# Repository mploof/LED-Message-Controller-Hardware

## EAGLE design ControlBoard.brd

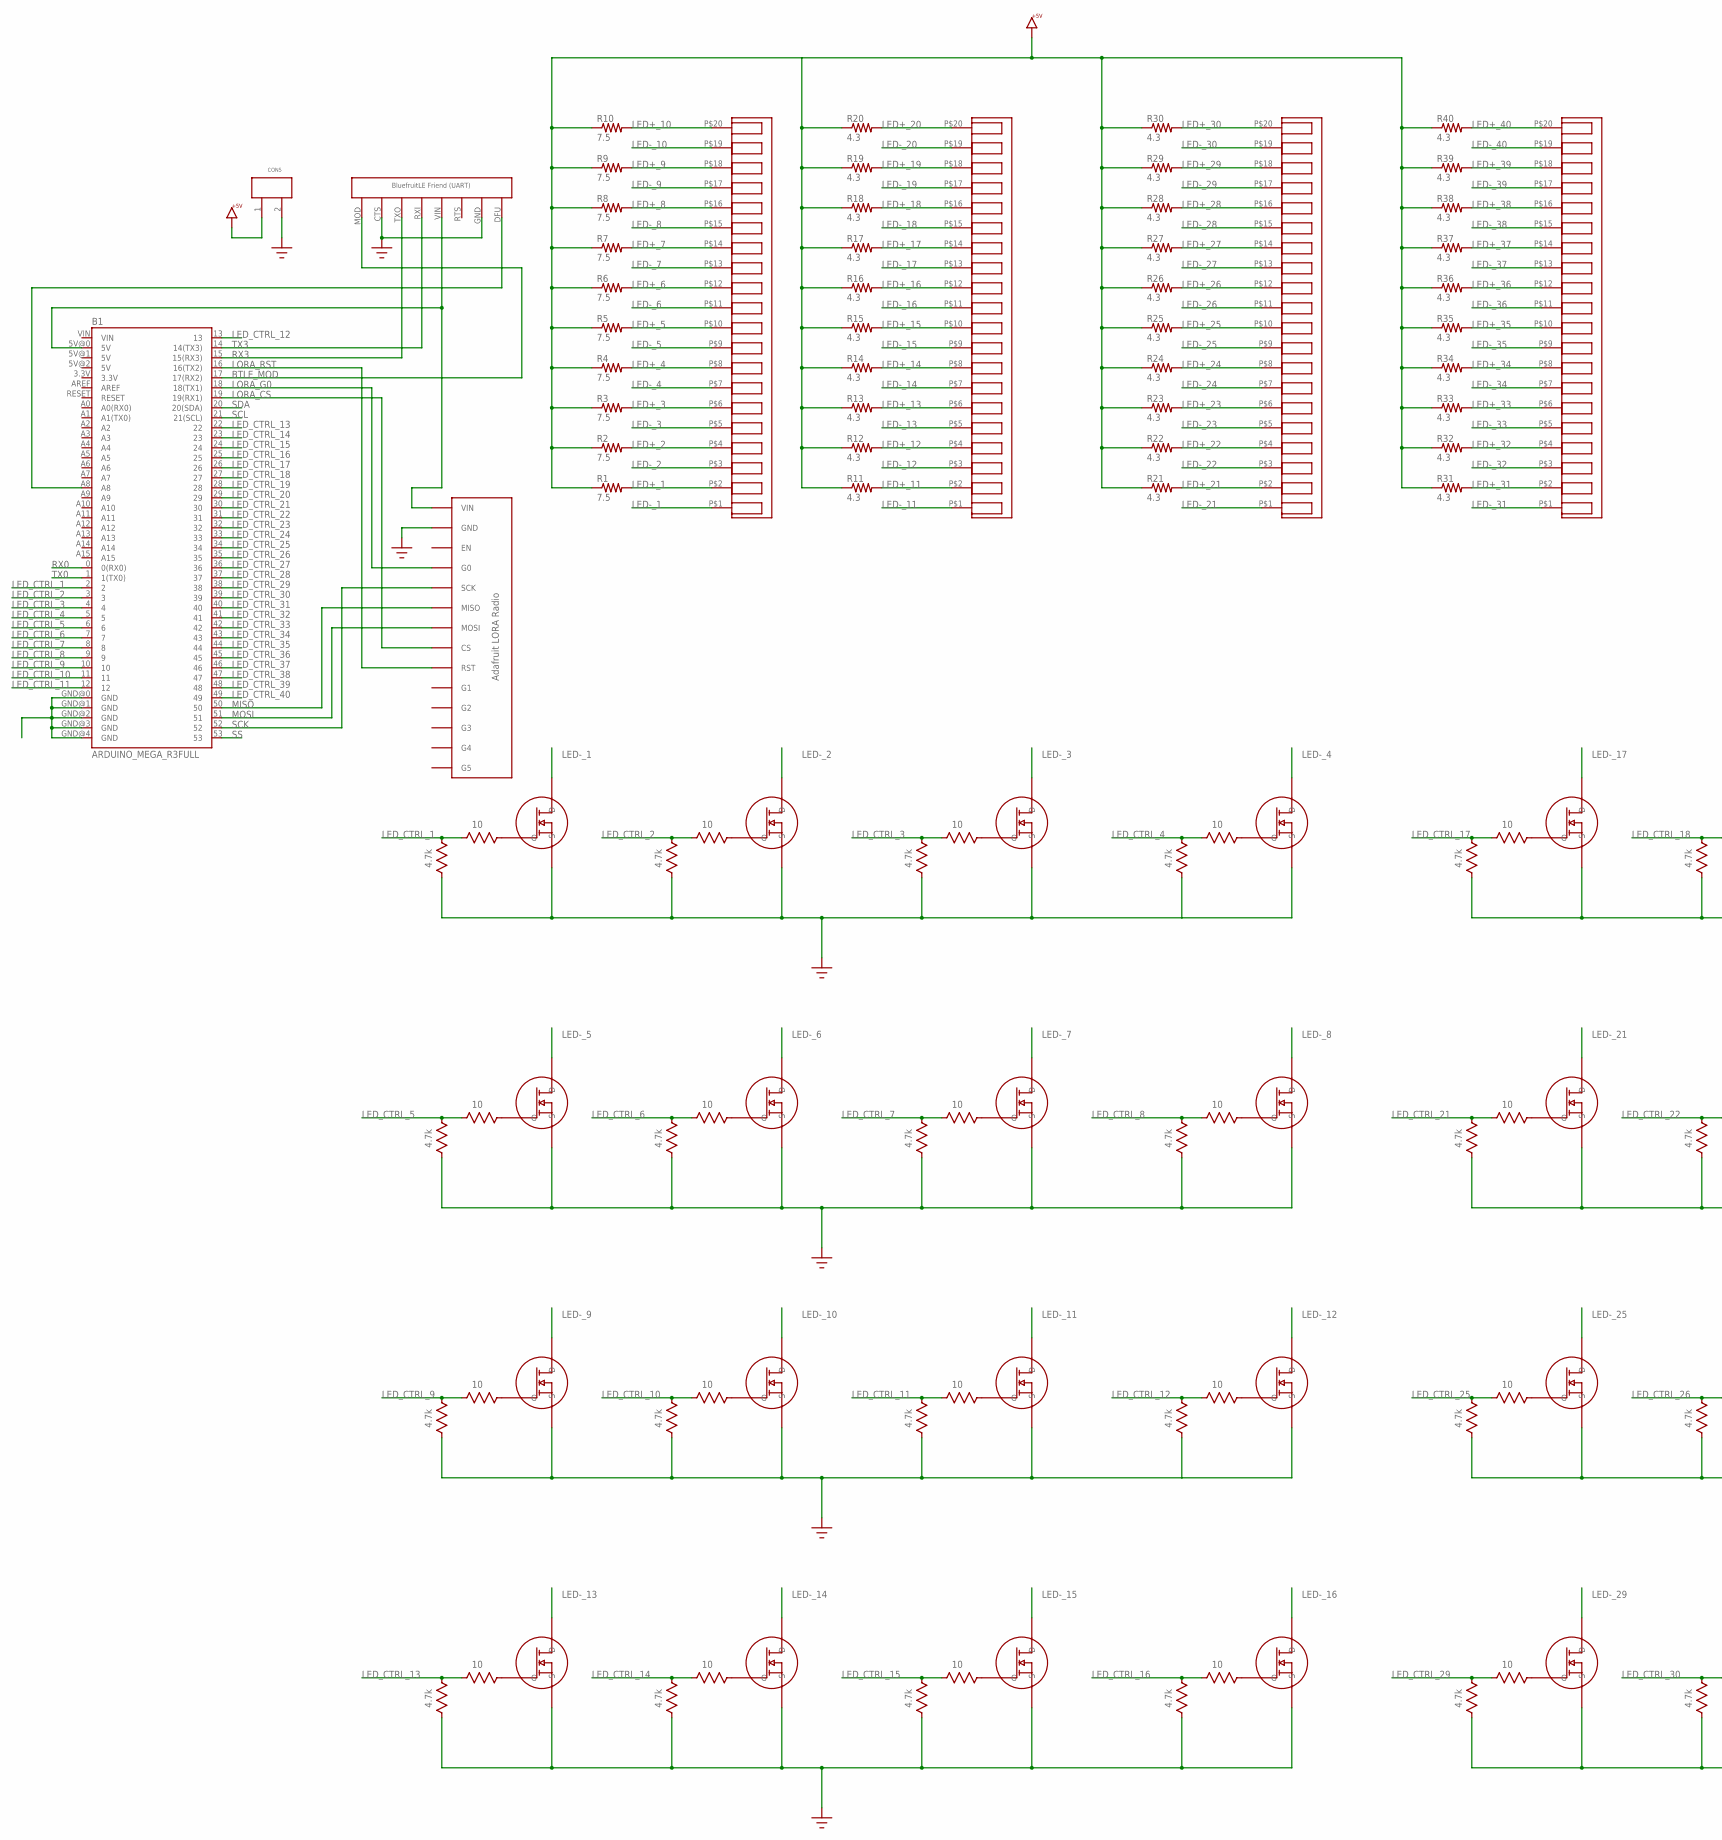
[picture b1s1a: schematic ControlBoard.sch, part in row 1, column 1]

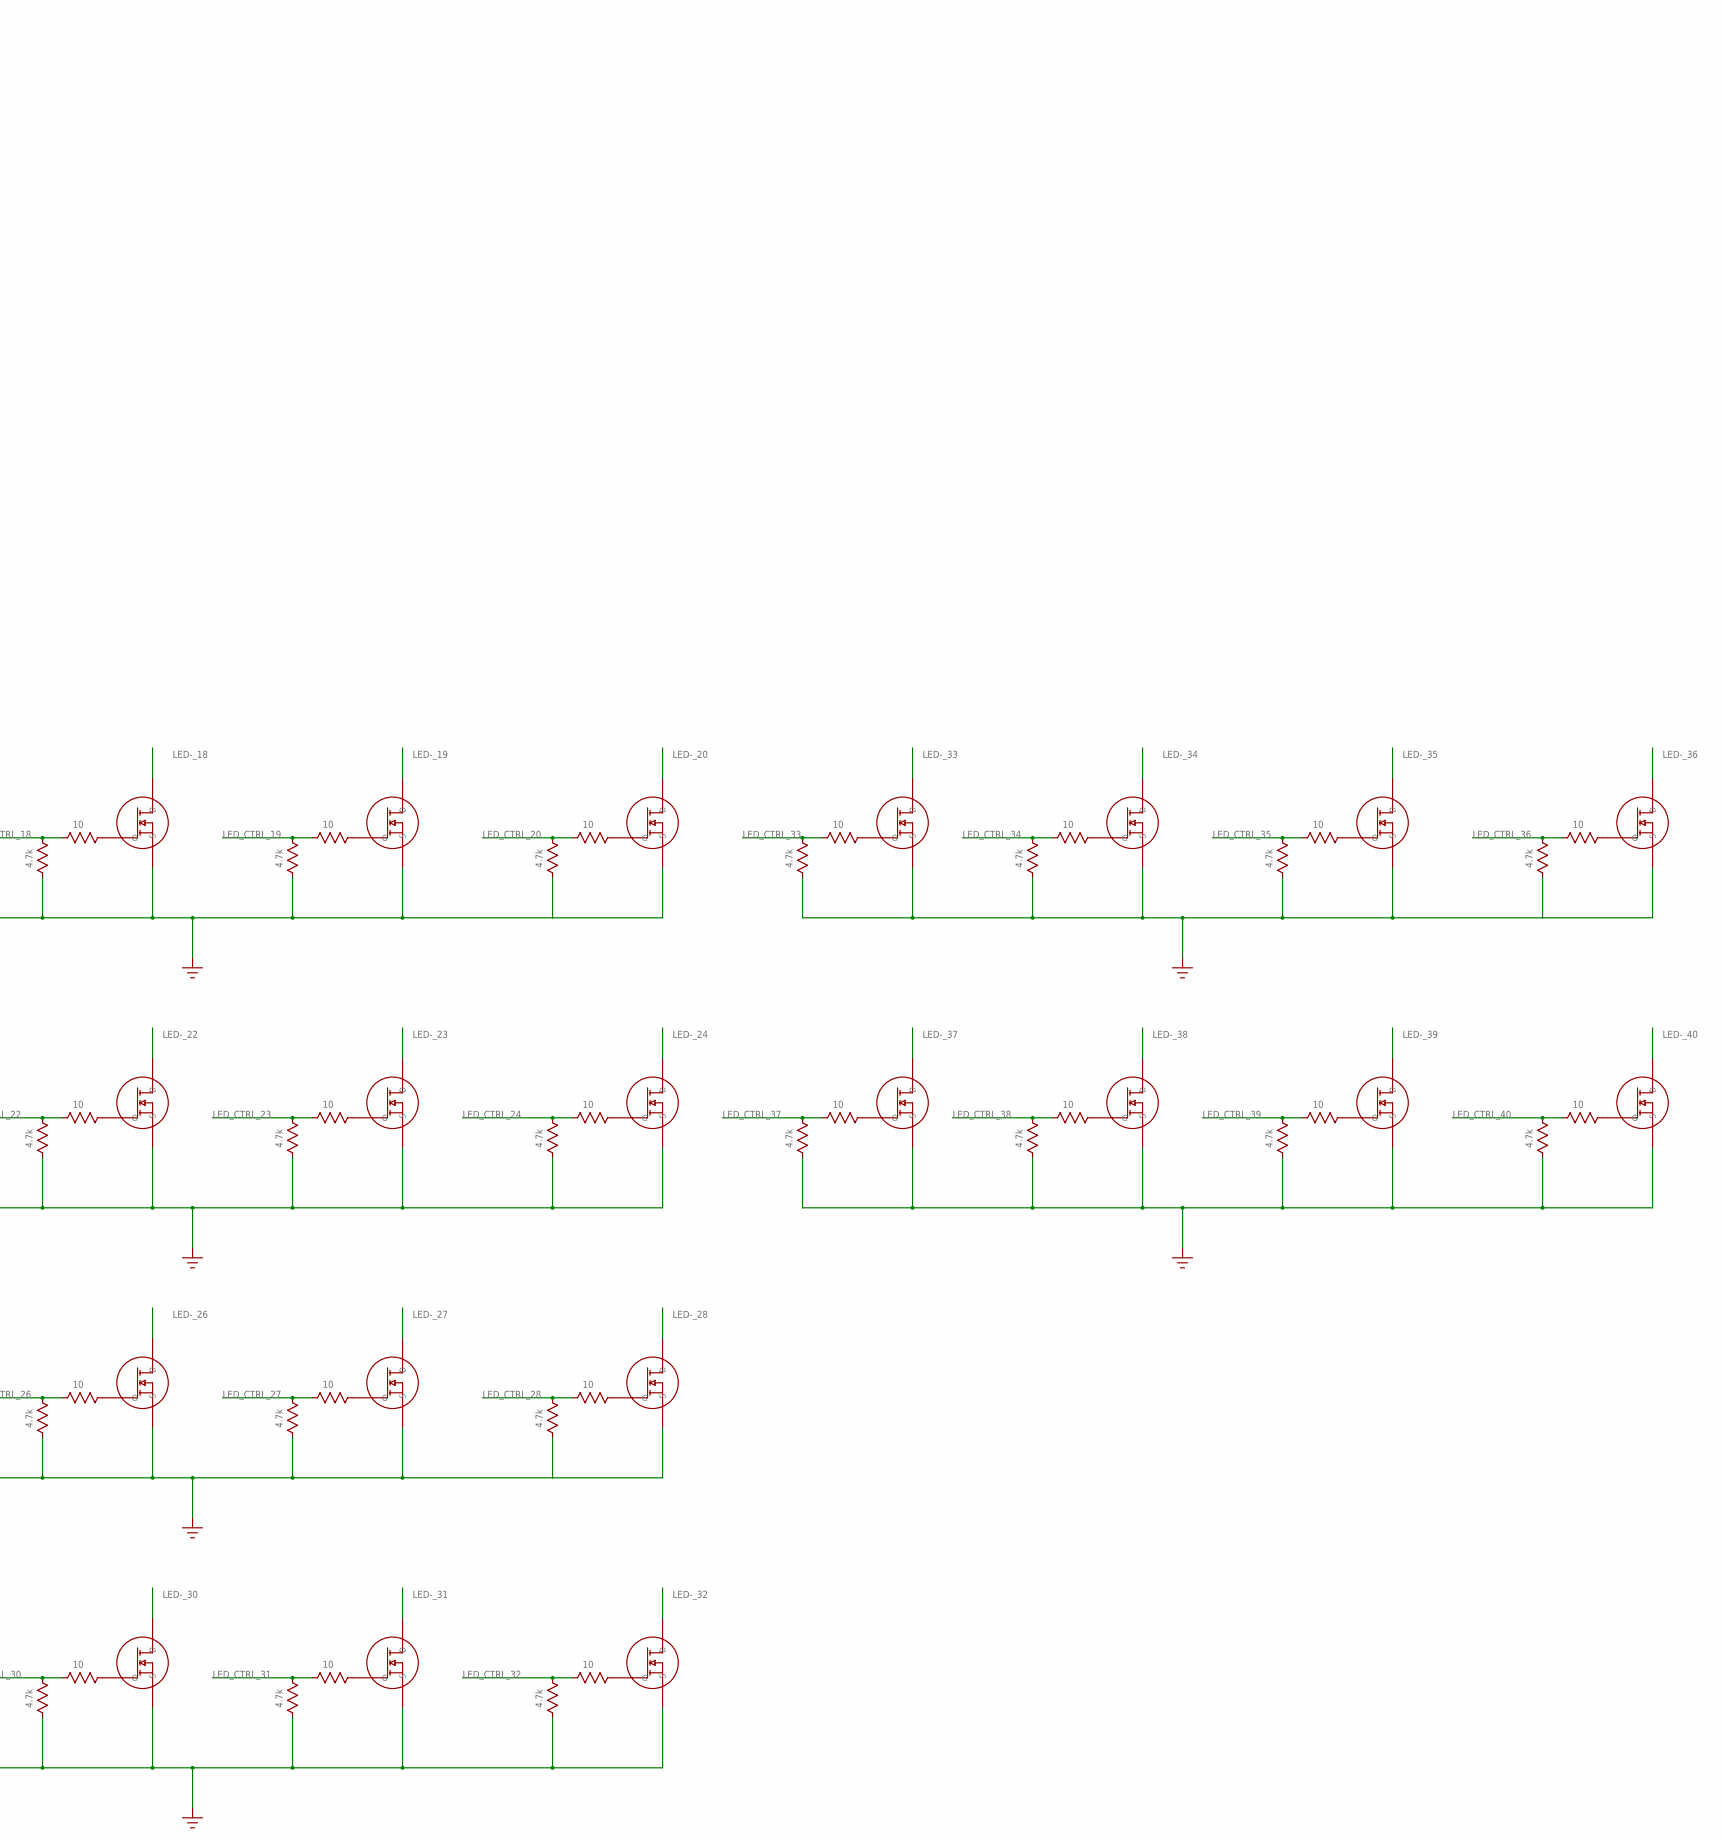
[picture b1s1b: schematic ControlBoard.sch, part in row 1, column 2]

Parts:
B1: ARDUINO_MEGA_R3FULL; ARDUINO_MEGA
CON1, CON2, CON3, CON4: CONN_20; SPRING_CAGE_X20_1990180
CON5: CONN_2; TERMINAL_BLOCK-2X_1792229
R1, R2, R3, R4, R5, R6, R7, R8, R9, R10: 7.5; RADIAL-RES-2W
R11, R12, R13, R14, R15, R16, R17, R18, R19, R20, R21, R22, R23, R24, R25, R26, R27, R28, R29, R30, R31, R32, R33, R34, R35, R36, R37, R38, R39, R40: 4.3; RADIAL-RES-2W
R41, R42, R43, R44, R45: 4.7k; 1506_X8
R46, R47, R48, R49, R50: 10; 1506_X8
U$1, U$2, U$3, U$4, U$5, U$6, U$7, U$8, U$9, U$10, U$15, U$16, U$17, U$18, U$19, U$20, U$21, U$22, U$27, U$28, U$29, U$30, U$31, U$32, U$37, U$38, U$39, U$40, U$41, U$42, U$43, U$44, U$49, U$50, U$51, U$52, U$53, U$54, U$55, U$56: MOSFET; SOT-23/TO-236
U$62: BLUEFRUIT_LE_FRIEND_UART
U$64: ADAFRUIT_LORA_RADIO

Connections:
+5V: CON5.1, R1.P$1 (1), R2.P$1 (1), R3.P$1 (1), R4.P$1 (1), R5.P$1 (1), R6.P$1 (1), R7.P$1 (1), R8.P$1 (1), R9.P$1 (1), R10.P$1 (1), R11.P$1 (1), R12.P$1 (1), R13.P$1 (1), R14.P$1 (1), R15.P$1 (1), R16.P$1 (1), R17.P$1 (1), R18.P$1 (1), R19.P$1 (1), R20.P$1 (1), R21.P$1 (1), R22.P$1 (1), R23.P$1 (1), R24.P$1 (1), R25.P$1 (1), R26.P$1 (1), R27.P$1 (1), R28.P$1 (1), R29.P$1 (1), R30.P$1 (1), R31.P$1 (1), R32.P$1 (1), R33.P$1 (1), R34.P$1 (1), R35.P$1 (1), R36.P$1 (1), R37.P$1 (1), R38.P$1 (1), R39.P$1 (1), R40.P$1 (1)
BTLE_DFU: B1.A8, U$62.DFU
BTLE_MOD: B1.17 (17(RX2)), U$62.MOD
GND: B1.GND@0 (GND), B1.GND@1 (GND), B1.GND@2 (GND), B1.GND@3 (GND), B1.GND@4 (GND), CON5.2, R41.P$1, R41.P$2, R41.P$3, R41.P$4, R41.P$5, R41.P$6, R41.P$7, R41.P$8, R42.P$1, R42.P$2, R42.P$3, R42.P$4, R42.P$5, R42.P$6, R42.P$7, R42.P$8, R43.P$1, R43.P$2, R43.P$3, R43.P$4, R43.P$5, R43.P$6, R43.P$7, R43.P$8, R44.P$1, R44.P$2, R44.P$3, R44.P$4, R44.P$5, R44.P$6, R44.P$7, R44.P$8, R45.P$1, R45.P$2, R45.P$3, R45.P$4, R45.P$5, R45.P$6, R45.P$7, R45.P$8, U$1.P$2 (S), U$2.P$2 (S), U$3.P$2 (S), U$4.P$2 (S), U$5.P$2 (S), U$6.P$2 (S), U$7.P$2 (S), U$8.P$2 (S), U$9.P$2 (S), U$10.P$2 (S), U$15.P$2 (S), U$16.P$2 (S), U$17.P$2 (S), U$18.P$2 (S), U$19.P$2 (S), U$20.P$2 (S), U$21.P$2 (S), U$22.P$2 (S), U$27.P$2 (S), U$28.P$2 (S), U$29.P$2 (S), U$30.P$2 (S), U$31.P$2 (S), U$32.P$2 (S), U$37.P$2 (S), U$38.P$2 (S), U$39.P$2 (S), U$40.P$2 (S), U$41.P$2 (S), U$42.P$2 (S), U$43.P$2 (S), U$44.P$2 (S), U$49.P$2 (S), U$50.P$2 (S), U$51.P$2 (S), U$52.P$2 (S), U$53.P$2 (S), U$54.P$2 (S), U$55.P$2 (S), U$56.P$2 (S), U$62.CTS, U$62.GND, U$64.P$2 (GND)
LED+_1: CON1.P$2 (2), R1.P$2 (2)
LED+_2: CON1.P$4 (4), R2.P$2 (2)
LED+_3: CON1.P$6 (6), R3.P$2 (2)
LED+_4: CON1.P$8 (8), R4.P$2 (2)
LED+_5: CON1.P$10 (10), R5.P$2 (2)
LED+_6: CON1.P$12 (12), R6.P$2 (2)
LED+_7: CON1.P$14 (14), R7.P$2 (2)
LED+_8: CON1.P$16 (16), R8.P$2 (2)
LED+_9: CON1.P$18 (18), R9.P$2 (2)
LED+_10: CON1.P$20 (20), R10.P$2 (2)
LED+_11: CON2.P$2 (2), R11.P$2 (2)
LED+_12: CON2.P$4 (4), R12.P$2 (2)
LED+_13: CON2.P$6 (6), R13.P$2 (2)
LED+_14: CON2.P$8 (8), R14.P$2 (2)
LED+_15: CON2.P$10 (10), R15.P$2 (2)
LED+_16: CON2.P$12 (12), R16.P$2 (2)
LED+_17: CON2.P$14 (14), R17.P$2 (2)
LED+_18: CON2.P$16 (16), R18.P$2 (2)
LED+_19: CON2.P$18 (18), R19.P$2 (2)
LED+_20: CON2.P$20 (20), R20.P$2 (2)
LED+_21: CON3.P$2 (2), R21.P$2 (2)
LED+_22: CON3.P$4 (4), R22.P$2 (2)
LED+_23: CON3.P$6 (6), R23.P$2 (2)
LED+_24: CON3.P$8 (8), R24.P$2 (2)
LED+_25: CON3.P$10 (10), R25.P$2 (2)
LED+_26: CON3.P$12 (12), R26.P$2 (2)
LED+_27: CON3.P$14 (14), R27.P$2 (2)
LED+_28: CON3.P$16 (16), R28.P$2 (2)
LED+_29: CON3.P$18 (18), R29.P$2 (2)
LED+_30: CON3.P$20 (20), R30.P$2 (2)
LED+_31: CON4.P$2 (2), R31.P$2 (2)
LED+_32: CON4.P$4 (4), R32.P$2 (2)
LED+_33: CON4.P$6 (6), R33.P$2 (2)
LED+_34: CON4.P$8 (8), R34.P$2 (2)
LED+_35: CON4.P$10 (10), R35.P$2 (2)
LED+_36: CON4.P$12 (12), R36.P$2 (2)
LED+_37: CON4.P$14 (14), R37.P$2 (2)
LED+_38: CON4.P$16 (16), R38.P$2 (2)
LED+_39: CON4.P$18 (18), R39.P$2 (2)
LED+_40: CON4.P$20 (20), R40.P$2 (2)
LED-_1: CON1.P$1 (1), U$3.P$3 (D)
LED-_2: CON1.P$3 (3), U$4.P$3 (D)
LED-_3: CON1.P$5 (5), U$5.P$3 (D)
LED-_4: CON1.P$7 (7), U$6.P$3 (D)
LED-_5: CON1.P$9 (9), U$7.P$3 (D)
LED-_6: CON1.P$11 (11), U$8.P$3 (D)
LED-_7: CON1.P$13 (13), U$9.P$3 (D)
LED-_8: CON1.P$15 (15), U$10.P$3 (D)
LED-_9: CON1.P$17 (17), U$15.P$3 (D)
LED-_10: CON1.P$19 (19), U$16.P$3 (D)
LED-_11: CON2.P$1 (1), U$17.P$3 (D)
LED-_12: CON2.P$3 (3), U$18.P$3 (D)
LED-_13: CON2.P$5 (5), U$19.P$3 (D)
LED-_14: CON2.P$7 (7), U$20.P$3 (D)
LED-_15: CON2.P$9 (9), U$21.P$3 (D)
LED-_16: CON2.P$11 (11), U$22.P$3 (D)
LED-_17: CON2.P$13 (13), U$1.P$3 (D)
LED-_18: CON2.P$15 (15), U$2.P$3 (D)
LED-_19: CON2.P$17 (17), U$27.P$3 (D)
LED-_20: CON2.P$19 (19), U$28.P$3 (D)
LED-_21: CON3.P$1 (1), U$29.P$3 (D)
LED-_22: CON3.P$3 (3), U$30.P$3 (D)
LED-_23: CON3.P$5 (5), U$31.P$3 (D)
LED-_24: CON3.P$7 (7), U$32.P$3 (D)
LED-_25: CON3.P$9 (9), U$37.P$3 (D)
LED-_26: CON3.P$11 (11), U$38.P$3 (D)
LED-_27: CON3.P$13 (13), U$39.P$3 (D)
LED-_28: CON3.P$15 (15), U$40.P$3 (D)
LED-_29: CON3.P$17 (17), U$41.P$3 (D)
LED-_30: CON3.P$19 (19), U$42.P$3 (D)
LED-_31: CON4.P$1 (1), U$43.P$3 (D)
LED-_32: CON4.P$3 (3), U$44.P$3 (D)
LED-_33: CON4.P$5 (5), U$49.P$3 (D)
LED-_34: CON4.P$7 (7), U$50.P$3 (D)
LED-_35: CON4.P$9 (9), U$51.P$3 (D)
LED-_36: CON4.P$11 (11), U$52.P$3 (D)
LED-_37: CON4.P$13 (13), U$53.P$3 (D)
LED-_38: CON4.P$15 (15), U$54.P$3 (D)
LED-_39: CON4.P$17 (17), U$55.P$3 (D)
LED-_40: CON4.P$19 (19), U$56.P$3 (D)
LED_CTRL_1: B1.2, R41.P$16, R46.P$1
LED_CTRL_2: B1.3, R41.P$15, R46.P$2
LED_CTRL_3: B1.4, R41.P$14, R46.P$3
LED_CTRL_4: B1.5, R41.P$13, R46.P$4
LED_CTRL_5: B1.6, R41.P$12, R46.P$5
LED_CTRL_6: B1.7, R41.P$11, R46.P$6
LED_CTRL_7: B1.8, R41.P$10, R46.P$7
LED_CTRL_8: B1.9, R41.P$9, R46.P$8
LED_CTRL_9: B1.10, R42.P$16, R47.P$1
LED_CTRL_10: B1.11, R42.P$15, R47.P$2
LED_CTRL_11: B1.12, R42.P$14, R47.P$3
LED_CTRL_12: B1.13, R42.P$13, R47.P$4
LED_CTRL_13: B1.22, R42.P$12, R47.P$5
LED_CTRL_14: B1.23, R42.P$11, R47.P$6
LED_CTRL_15: B1.24, R42.P$10, R47.P$7
LED_CTRL_16: B1.25, R42.P$9, R47.P$8
LED_CTRL_17: B1.26, R43.P$16, R48.P$1
LED_CTRL_18: B1.27, R43.P$15, R48.P$2
LED_CTRL_19: B1.28, R43.P$14, R48.P$3
LED_CTRL_20: B1.29, R43.P$13, R48.P$4
LED_CTRL_21: B1.30, R43.P$12, R48.P$5
LED_CTRL_22: B1.31, R43.P$11, R48.P$6
LED_CTRL_23: B1.32, R43.P$10, R48.P$7
LED_CTRL_24: B1.33, R43.P$9, R48.P$8
LED_CTRL_25: B1.34, R44.P$16, R49.P$1
LED_CTRL_26: B1.35, R44.P$15, R49.P$2
LED_CTRL_27: B1.36, R44.P$14, R49.P$3
LED_CTRL_28: B1.37, R44.P$13, R49.P$4
LED_CTRL_29: B1.38, R44.P$12, R49.P$5
LED_CTRL_30: B1.39, R44.P$11, R49.P$6
LED_CTRL_31: B1.40, R44.P$10, R49.P$7
LED_CTRL_32: B1.41, R44.P$9, R49.P$8
LED_CTRL_33: B1.42, R45.P$16, R50.P$1
LED_CTRL_34: B1.43, R45.P$15, R50.P$2
LED_CTRL_35: B1.44, R45.P$14, R50.P$3
LED_CTRL_36: B1.45, R45.P$13, R50.P$4
LED_CTRL_37: B1.46, R45.P$12, R50.P$5
LED_CTRL_38: B1.47, R45.P$11, R50.P$6
LED_CTRL_39: B1.48, R45.P$10, R50.P$7
LED_CTRL_40: B1.49, R45.P$9, R50.P$8
LORA_CS: B1.19 (19(RX1)), U$64.P$8 (CS)
LORA_G0: B1.18 (18(TX1)), U$64.P$4 (G0)
LORA_RST: B1.16 (16(TX2)), U$64.P$9 (RST)
MCU_5V: B1.5V@0 (5V), U$62.VIN, U$64.P$1 (VIN)
MISO: B1.50, U$64.P$6 (MISO)
MOSI: B1.51, U$64.P$7 (MOSI)
unnamed: R46.P$16, U$3.P$1 (G)
unnamed: R46.P$15, U$4.P$1 (G)
unnamed: R46.P$14, U$5.P$1 (G)
unnamed: R46.P$13, U$6.P$1 (G)
unnamed: R46.P$12, U$7.P$1 (G)
unnamed: R46.P$11, U$8.P$1 (G)
unnamed: R46.P$10, U$9.P$1 (G)
unnamed: R46.P$9, U$10.P$1 (G)
unnamed: R47.P$16, U$15.P$1 (G)
unnamed: R47.P$15, U$16.P$1 (G)
unnamed: R47.P$14, U$17.P$1 (G)
unnamed: R47.P$13, U$18.P$1 (G)
unnamed: R47.P$12, U$19.P$1 (G)
unnamed: R47.P$11, U$20.P$1 (G)
unnamed: R47.P$10, U$21.P$1 (G)
unnamed: R47.P$9, U$22.P$1 (G)
unnamed: R48.P$16, U$1.P$1 (G)
unnamed: R48.P$15, U$2.P$1 (G)
unnamed: R48.P$14, U$27.P$1 (G)
unnamed: R48.P$13, U$28.P$1 (G)
unnamed: R48.P$12, U$29.P$1 (G)
unnamed: R48.P$11, U$30.P$1 (G)
unnamed: R48.P$10, U$31.P$1 (G)
unnamed: R48.P$9, U$32.P$1 (G)
unnamed: R49.P$16, U$37.P$1 (G)
unnamed: R49.P$15, U$38.P$1 (G)
unnamed: R49.P$14, U$39.P$1 (G)
unnamed: R49.P$13, U$40.P$1 (G)
unnamed: R49.P$12, U$41.P$1 (G)
unnamed: R49.P$11, U$42.P$1 (G)
unnamed: R49.P$10, U$43.P$1 (G)
unnamed: R49.P$9, U$44.P$1 (G)
unnamed: R50.P$16, U$49.P$1 (G)
unnamed: R50.P$15, U$50.P$1 (G)
unnamed: R50.P$14, U$51.P$1 (G)
unnamed: R50.P$13, U$52.P$1 (G)
unnamed: R50.P$12, U$53.P$1 (G)
unnamed: R50.P$11, U$54.P$1 (G)
unnamed: R50.P$10, U$55.P$1 (G)
unnamed: R50.P$9, U$56.P$1 (G)
RX0: B1.0 (0(RX0))
RX3: B1.15 (15(RX3)), U$62.TXO
SCK: B1.52, U$64.P$5 (SCK)
SCL: B1.21 (21(SCL))
SDA: B1.20 (20(SDA))
SS: B1.53
TX0: B1.1 (1(TX0))
TX3: B1.14 (14(TX3)), U$62.RXI

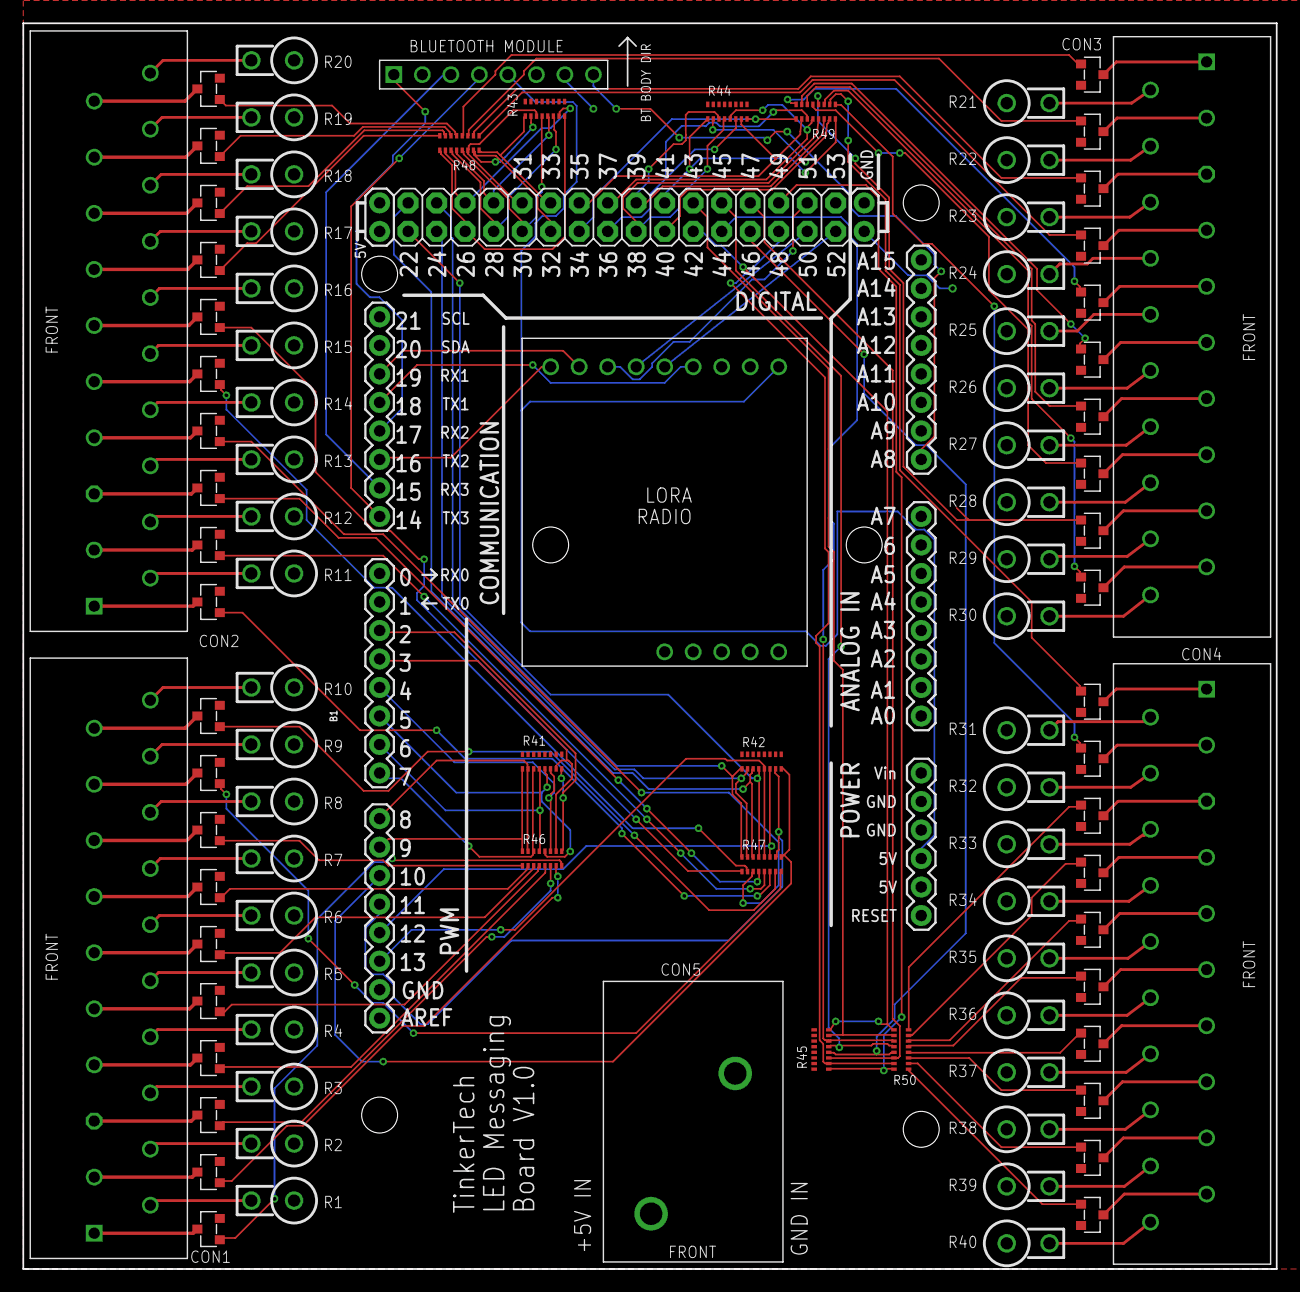
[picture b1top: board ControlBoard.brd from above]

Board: 2 copper layers, 111.7 x 111.0 mm, 98 parts (0 on the bottom side), 173 nets.

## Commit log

2017-07-21 Added Eagle .gitignore
2017-07-26 Initial commit
    Not yet fully routed
2017-07-26 Removed lots of routes
2017-08-08 Final refinements before first order
    — Connected DFU and MOD pins of BLE UART board
    — Tented vias
    — Fixed DRC stop mask errors

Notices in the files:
parts and their libraries:
SparkFun-Boards: Licensing: Creative Commons ShareAlike 4.0 International - https://creativecommons.org/licenses/by-sa/4.0
